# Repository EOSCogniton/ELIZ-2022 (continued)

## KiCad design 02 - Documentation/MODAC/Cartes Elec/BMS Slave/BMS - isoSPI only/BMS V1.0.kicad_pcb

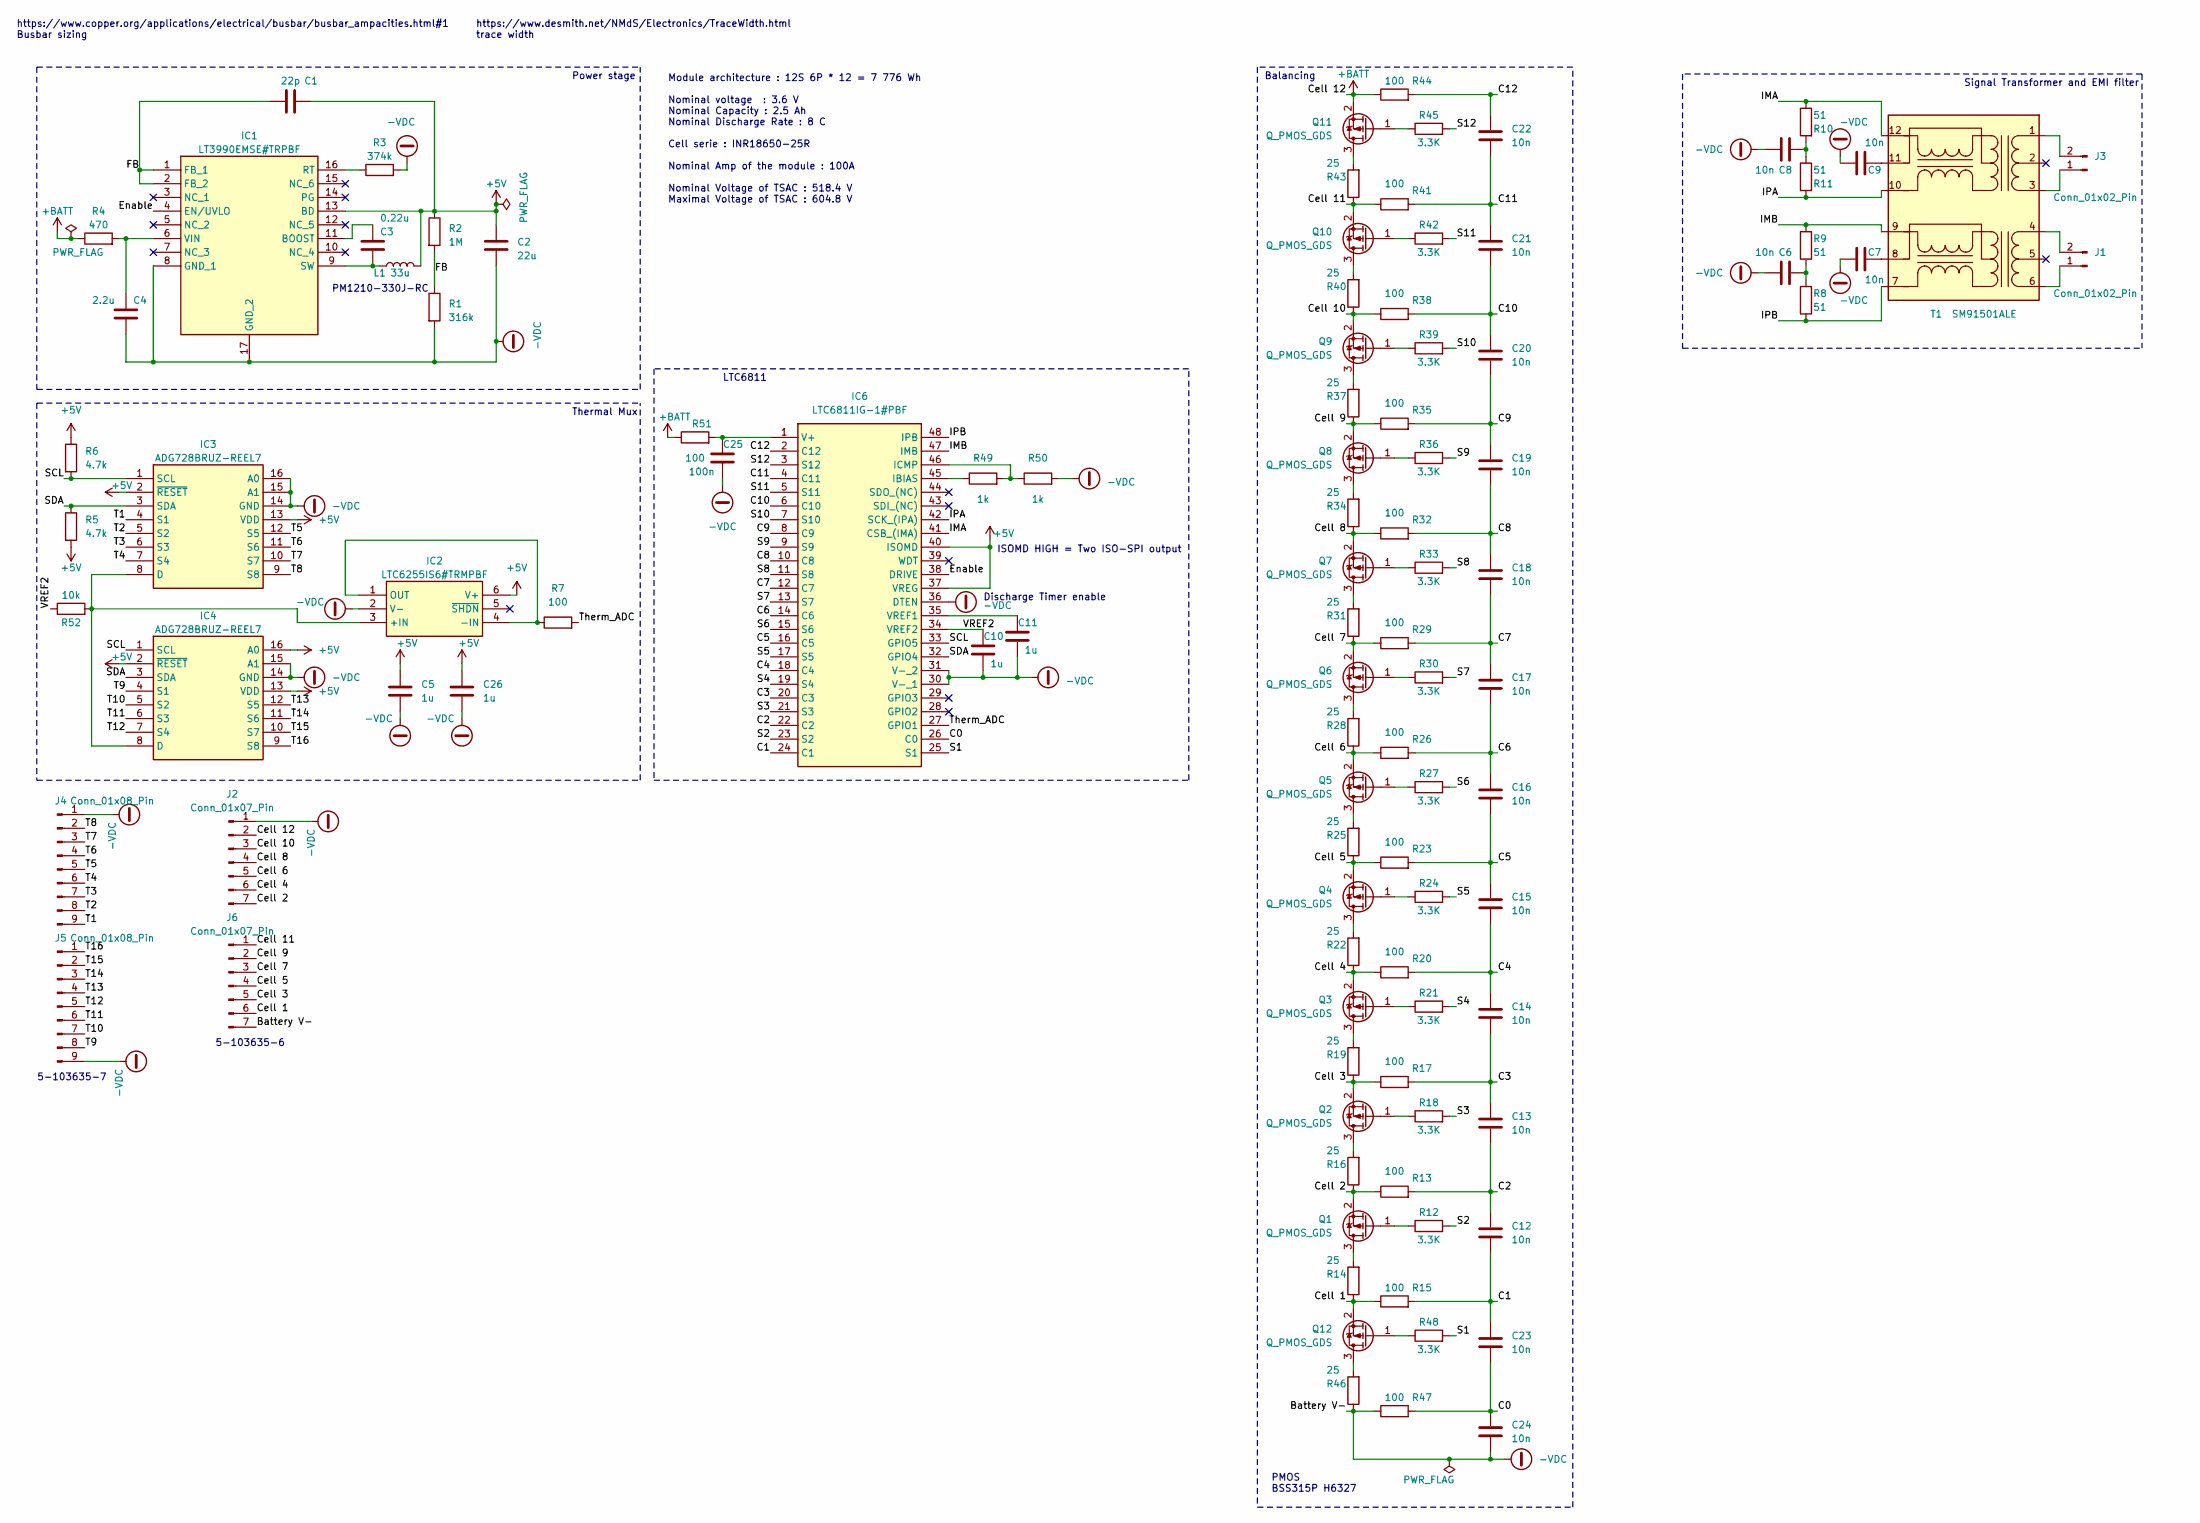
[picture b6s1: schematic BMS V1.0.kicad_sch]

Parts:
C1: 22p; C_0805_2012Metric_Pad1.18x1.45mm_HandSolder
C2: 22u; C_0805_2012Metric_Pad1.18x1.45mm_HandSolder
C3: 0.22u; C_0805_2012Metric_Pad1.18x1.45mm_HandSolder
C4: 2.2u; C_0805_2012Metric_Pad1.18x1.45mm_HandSolder
C5, C10, C11, C26: 1u; C_0805_2012Metric_Pad1.18x1.45mm_HandSolder
C6, C7, C8, C9, C12, C13, C14, C15, C16, C17, C18, C19, C20, C21, C22, C23, C24: 10n; C_0805_2012Metric_Pad1.18x1.45mm_HandSolder
C25: 100n; C_0805_2012Metric_Pad1.18x1.45mm_HandSolder
IC1: LT3990EMSE#TRPBF; SOP50P490X110-17N; Mouser Part Number 584-LT3990EMSE#TRPBF
IC2: LTC6255IS6#TRMPBF; SOT95P280X100-6N; Mouser Part Number 584-LTC6255IS6TRMPBF
IC3, IC4: ADG728BRUZ-REEL7; SOP65P640X120-16N; Mouser Part Number 584-ADG728BRUZ-R7
IC6: LTC6811IG-1#PBF; SOP50P780X200-48N; Mouser Part Number 584-LTC6811IG-1#PBF
J1, J3: Conn_01x02_Pin; RHDR2W97P0X254_1X2_654X508X1379P
J2, J6: Conn_01x07_Pin; SHDRRA7W77P0X254_1X7_2032X1359X699P
J4, J5: Conn_01x08_Pin; SHDRRA9W69P0X254_1X9_2527X1359X741P
L1: 33u; L_1210_3225Metric_Pad1.42x2.65mm_HandSolder
Q1, Q2, Q3, Q4, Q5, Q6, Q7, Q8, Q9, Q10, Q11, Q12: Q_PMOS_GDS; SOT-23-3
R1: 316k; R_1206_3216Metric_Pad1.30x1.75mm_HandSolder
R2: 1M; R_1206_3216Metric_Pad1.30x1.75mm_HandSolder
R3: 374k; R_1206_3216Metric_Pad1.30x1.75mm_HandSolder
R4: 470; R_1206_3216Metric_Pad1.30x1.75mm_HandSolder
R5, R6: 4.7k; R_1206_3216Metric_Pad1.30x1.75mm_HandSolder
R7, R13, R15, R17, R20, R23, R26, R29, R32, R35, R38, R41, R44, R47, R51: 100; R_1206_3216Metric_Pad1.30x1.75mm_HandSolder
R8, R9, R10, R11: 51; R_1206_3216Metric_Pad1.30x1.75mm_HandSolder
R12, R18, R21, R24, R27, R30, R33, R36, R39, R42, R45, R48: 3.3K; R_1206_3216Metric_Pad1.30x1.75mm_HandSolder
R14, R16, R19, R22, R25, R28, R31, R34, R37, R40, R43, R46: 25; R_2512_6332Metric_Pad1.40x3.35mm_HandSolder
R49, R50: 1k; R_1206_3216Metric_Pad1.30x1.75mm_HandSolder
R52: 10k; R_1206_3216Metric_Pad1.30x1.75mm_HandSolder
T1: SM91501ALE; SOP200P1473X500-12N; Mouser Part Number 652-SM91501ALE

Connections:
+5V: C1.2, C2.2, C5.1, C26.1, IC1.13 (BD), IC2.6 (V+), IC3.2 (~RESET), IC3.13 (VDD), IC4.2 (~RESET), IC4.13 (VDD), IC4.16 (A0), IC6.37 (VREG), IC6.40 (ISOMD), L1.2, R2.1, R5.2, R6.1
+BATT: J2.2, Q11.2 (S), R4.1, R44.1, R51.1
-VDC: C2.1, C4.1, C5.2, C6.1, C7.1, C8.1, C9.1, C10.2, C11.2, C24.2, C25.2, C26.2, IC1.8 (GND_1), IC1.17 (GND_2), IC2.2 (V-), IC3.14 (GND), IC3.15 (A1), IC3.16 (A0), IC4.14 (GND), IC4.15 (A1), IC6.30 (V-_1), IC6.31 (V-_2), IC6.36 (DTEN), J2.1, J4.1, J5.9, J6.7, R1.2, R3.2, R46.1, R47.1, R50.2
/C0: C23.2, C24.1, IC6.26 (C0), R47.2
/C1: C12.2, C23.1, IC6.24 (C1), R15.2
/C2: C12.1, C13.2, IC6.22 (C2), R13.2
/C3: C13.1, C14.2, IC6.20 (C3), R17.2
/C4: C14.1, C15.2, IC6.18 (C4), R20.2
/C5: C15.1, C16.2, IC6.16 (C5), R23.2
/C6: C16.1, C17.2, IC6.14 (C6), R26.2
/C7: C17.1, C18.2, IC6.12 (C7), R29.2
/C8: C18.1, C19.2, IC6.10 (C8), R32.2
/C9: C19.1, C20.2, IC6.8 (C9), R35.2
/C10: C20.1, C21.2, IC6.6 (C10), R38.2
/C11: C21.1, C22.2, IC6.4 (C11), R41.2
/C12: C22.1, IC6.2 (C12), R44.2
/Cell 1: J6.6, Q12.2 (S), R14.1, R15.1
/Cell 2: J2.7, Q1.2 (S), R13.1, R16.1
/Cell 3: J6.5, Q2.2 (S), R17.1, R19.1
/Cell 4: J2.6, Q3.2 (S), R20.1, R22.1
/Cell 5: J6.4, Q4.2 (S), R23.1, R25.1
/Cell 6: J2.5, Q5.2 (S), R26.1, R28.1
/Cell 7: J6.3, Q6.2 (S), R29.1, R31.1
/Cell 8: J2.4, Q7.2 (S), R32.1, R34.1
/Cell 9: J6.2, Q8.2 (S), R35.1, R37.1
/Cell 10: J2.3, Q9.2 (S), R38.1, R40.1
/Cell 11: J6.1, Q10.2 (S), R41.1, R43.1
/Enable: IC1.4 (EN/UVLO), IC6.38 (DRIVE)
/FB: C1.1, IC1.1 (FB_1), IC1.2 (FB_2), R1.1, R2.2
/IMA: IC6.41 (CSB_(IMA)), R10.1, T1.12 (SEC1_3)
/IMB: IC6.47 (IMB), R9.2, T1.9 (SEC2_3)
/IPA: IC6.42 (SCK_(IPA)), R11.2, T1.10 (SEC1_1)
/IPB: IC6.48 (IPB), R8.1, T1.7 (SEC2_1)
/S1: IC6.25 (S1), R48.2
/S2: IC6.23 (S2), R12.2
/S3: IC6.21 (S3), R18.2
/S4: IC6.19 (S4), R21.2
/S5: IC6.17 (S5), R24.2
/S6: IC6.15 (S6), R27.2
/S7: IC6.13 (S7), R30.2
/S8: IC6.11 (S8), R33.2
/S9: IC6.9 (S9), R36.2
/S10: IC6.7 (S10), R39.2
/S11: IC6.5 (S11), R42.2
/S12: IC6.3 (S12), R45.2
/SCL: IC3.1 (SCL), IC4.1 (SCL), IC6.33 (GPIO5), R6.2
/SDA: IC3.3 (SDA), IC4.3 (SDA), IC6.32 (GPIO4), R5.1
/T1: IC3.4 (S1), J4.9
/T2: IC3.5 (S2), J4.8
/T3: IC3.6 (S3), J4.7
/T4: IC3.7 (S4), J4.6
/T5: IC3.12 (S5), J4.5
/T6: IC3.11 (S6), J4.4
/T7: IC3.10 (S7), J4.3
/T8: IC3.9 (S8), J4.2
/T9: IC4.4 (S1), J5.8
/T10: IC4.5 (S2), J5.7
/T11: IC4.6 (S3), J5.6
/T12: IC4.7 (S4), J5.5
/T13: IC4.12 (S5), J5.4
/T14: IC4.11 (S6), J5.3
/T15: IC4.10 (S7), J5.2
/T16: IC4.9 (S8), J5.1
/Therm_ADC: IC6.27 (GPIO1), R7.2
/VREF2: C10.1, IC6.34 (VREF2), R52.1
unnamed: C6.2, R8.2, R9.1
unnamed: C8.2, R10.2, R11.1
unnamed: C3.2, IC1.11 (BOOST)
unnamed: IC1.16 (RT), R3.1
unnamed: C3.1, IC1.9 (SW), L1.1
unnamed: C4.2, IC1.6 (VIN), R4.2
unnamed: IC2.3 (+IN), IC3.8 (D), IC4.8 (D), R52.2
unnamed: IC2.1 (OUT), IC2.4 (-IN), R7.1
unnamed: IC6.45 (IBIAS), R49.1
unnamed: IC6.46 (ICMP), R49.2, R50.1
unnamed: C25.1, IC6.1 (V+), R51.2
unnamed: C11.1, IC6.35 (VREF1)
unnamed: J1.1, T1.6 (PRI2_3)
unnamed: J1.2, T1.4 (PRI2_1)
unnamed: J3.1, T1.3 (PRI1_3)
unnamed: J3.2, T1.1 (PRI1_1)
unnamed: Q1.3 (D), R14.2
unnamed: Q1.1 (G), R12.1
unnamed: Q2.3 (D), R16.2
unnamed: Q2.1 (G), R18.1
unnamed: Q3.3 (D), R19.2
unnamed: Q3.1 (G), R21.1
unnamed: Q4.3 (D), R22.2
unnamed: Q4.1 (G), R24.1
unnamed: Q5.3 (D), R25.2
unnamed: Q5.1 (G), R27.1
unnamed: Q6.3 (D), R28.2
unnamed: Q6.1 (G), R30.1
unnamed: Q7.3 (D), R31.2
unnamed: Q7.1 (G), R33.1
unnamed: Q8.3 (D), R34.2
unnamed: Q8.1 (G), R36.1
unnamed: Q9.3 (D), R37.2
unnamed: Q9.1 (G), R39.1
unnamed: Q10.3 (D), R40.2
unnamed: Q10.1 (G), R42.1
unnamed: Q11.3 (D), R43.2
unnamed: Q11.1 (G), R45.1
unnamed: Q12.3 (D), R46.2
unnamed: Q12.1 (G), R48.1
unnamed: C9.2, T1.11 (SEC1_2)
unnamed: C7.2, T1.8 (SEC2_2)

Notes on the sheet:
Module architecture : 12S 6P * 12 = 7 776 Wh Nominal voltage : 3.6 V Nominal Capacity : 2.5 Ah Nominal Discharge Rate : 8 C Cell serie : INR18650-25R Nominal Amp of the module : 100A Nominal Voltage of TSAC : 518.4 V Maximal Voltage of TSAC : 604.8 V
PMOS BSS315P H6327
PM1210-330J-RC
Balancing
Thermal Mux
Power stage
Signal Transformer and EMI filter
LTC6811
https://www.desmith.net/NMdS/Electronics/TraceWidth.html trace width
5-103635-7
https://www.copper.org/applications/electrical/busbar/busbar_ampacities.html#1 Busbar sizing
5-103635-6
ISOMD HIGH = Two ISO-SPI output
Discharge Timer enable

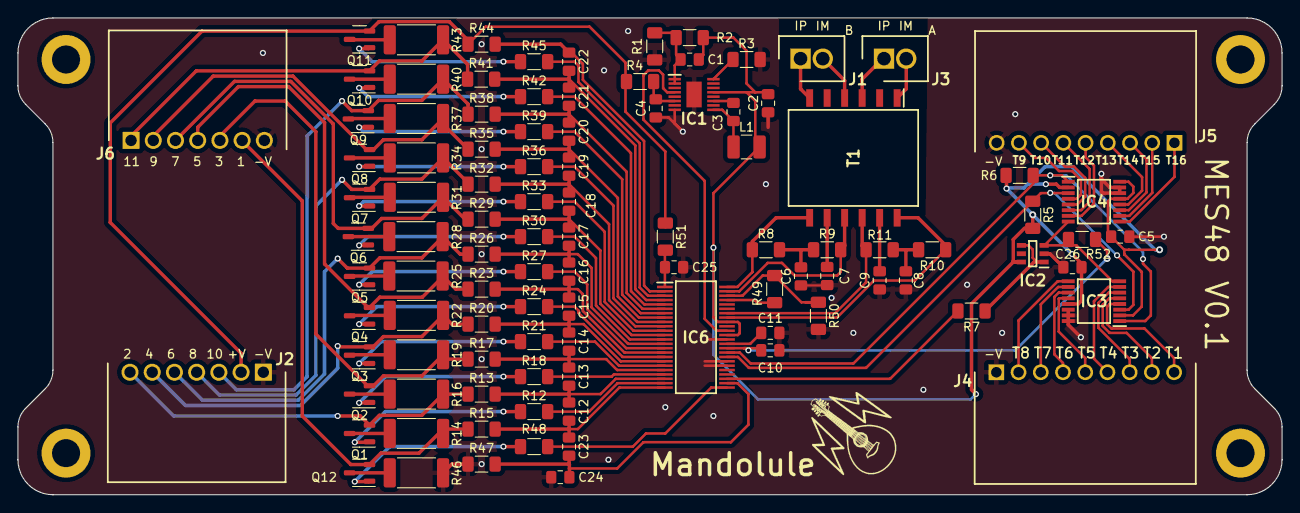
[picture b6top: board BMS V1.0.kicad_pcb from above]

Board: 2 copper layers, 144.5 x 54.5 mm, 104 parts (0 on the bottom side), 107 nets.

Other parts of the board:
Ref**: Val**; Mandolule Silk

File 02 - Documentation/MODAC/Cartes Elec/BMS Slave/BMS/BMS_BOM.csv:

"Designator","Comment","Footprint"
"C1","22p","Capacitor_SMD:C_0805_2012Metric_Pad1.18x1.45mm_HandSolder"
"C2","22u","Capacitor_SMD:C_0805_2012Metric_Pad1.18x1.45mm_HandSolder"
"C3","0.22u","Capacitor_SMD:C_0805_2012Metric_Pad1.18x1.45mm_HandSolder"
"C4","2.2u","Capacitor_SMD:C_0805_2012Metric_Pad1.18x1.45mm_HandSolder"
"C5,C10,C11,C26","1u","Capacitor_SMD:C_0805_2012Metric_Pad1.18x1.45mm_HandSolder"
"C6,C7,C8,C9,C12,C13,C14,C15,C16,C17,C18,C19,C20,C21,C22,C23,C24","10n","Capacitor_SMD:C_0805_2012Metric_Pad1.18x1.45mm_HandSolder"
"C25","100n","Capacitor_SMD:C_0805_2012Metric_Pad1.18x1.45mm_HandSolder"
"IC1","LT3990EMSE#TRPBF","EPSA:SOP50P490X110-17N"
"IC2","LTC6255IS6#TRMPBF","EPSA:SOT95P280X100-6N"
"IC3,IC4","ADG728BRUZ-REEL7","EPSA:SOP65P640X120-16N"
"IC6","LTC6811IG-1#PBF","EPSA:SOP50P780X200-48N"
"J1,J3","Conn_01x02_Pin","EPSA:RHDR2W97P0X254_1X2_654X508X1379P"
"J2,J6","Conn_01x07_Pin","EPSA:SHDRRA7W77P0X254_1X7_2032X1359X699P"
"J4,J5","Conn_01x08_Pin","EPSA:SHDRRA9W69P0X254_1X9_2527X1359X741P"
"L1","33u","Inductor_SMD:L_1210_3225Metric_Pad1.42x2.65mm_HandSolder"
"Q1,Q2,Q3,Q4,Q5,Q6,Q7,Q8,Q9,Q10,Q11,Q12","Q_PMOS_GDS","EPSA:SOT-23-3"
"R1","316k","Resistor_SMD:R_1206_3216Metric_Pad1.30x1.75mm_HandSolder"
"R2","1M","Resistor_SMD:R_1206_3216Metric_Pad1.30x1.75mm_HandSolder"
"R3","374k","Resistor_SMD:R_1206_3216Metric_Pad1.30x1.75mm_HandSolder"
"R4","470","Resistor_SMD:R_1206_3216Metric_Pad1.30x1.75mm_HandSolder"
"R5,R6","4.7k","Resistor_SMD:R_1206_3216Metric_Pad1.30x1.75mm_HandSolder"
"R7,R13,R15,R17,R20,R23,R26,R29,R32,R35,R38,R41,R44,R47,R51","100","Resistor_SMD:R_1206_3216Metric_Pad1.30x1.75mm_HandSolder"
"R8,R9,R10,R11","51","Resistor_SMD:R_1206_3216Metric_Pad1.30x1.75mm_HandSolder"
"R12,R18,R21,R24,R27,R30,R33,R36,R39,R42,R45,R48","3.3K","Resistor_SMD:R_1206_3216Metric_Pad1.30x1.75mm_HandSolder"
"R14,R16,R19,R22,R25,R28,R31,R34,R37,R40,R43,R46","25","Resistor_SMD:R_2512_6332Metric_Pad1.40x3.35mm_HandSolder"
"R49,R50","1k","Resistor_SMD:R_1206_3216Metric_Pad1.30x1.75mm_HandSolder"
"R52","10k","Resistor_SMD:R_1206_3216Metric_Pad1.30x1.75mm_HandSolder"
"T1","SM91501ALE","EPSA:SOP200P1473X500-12N"
